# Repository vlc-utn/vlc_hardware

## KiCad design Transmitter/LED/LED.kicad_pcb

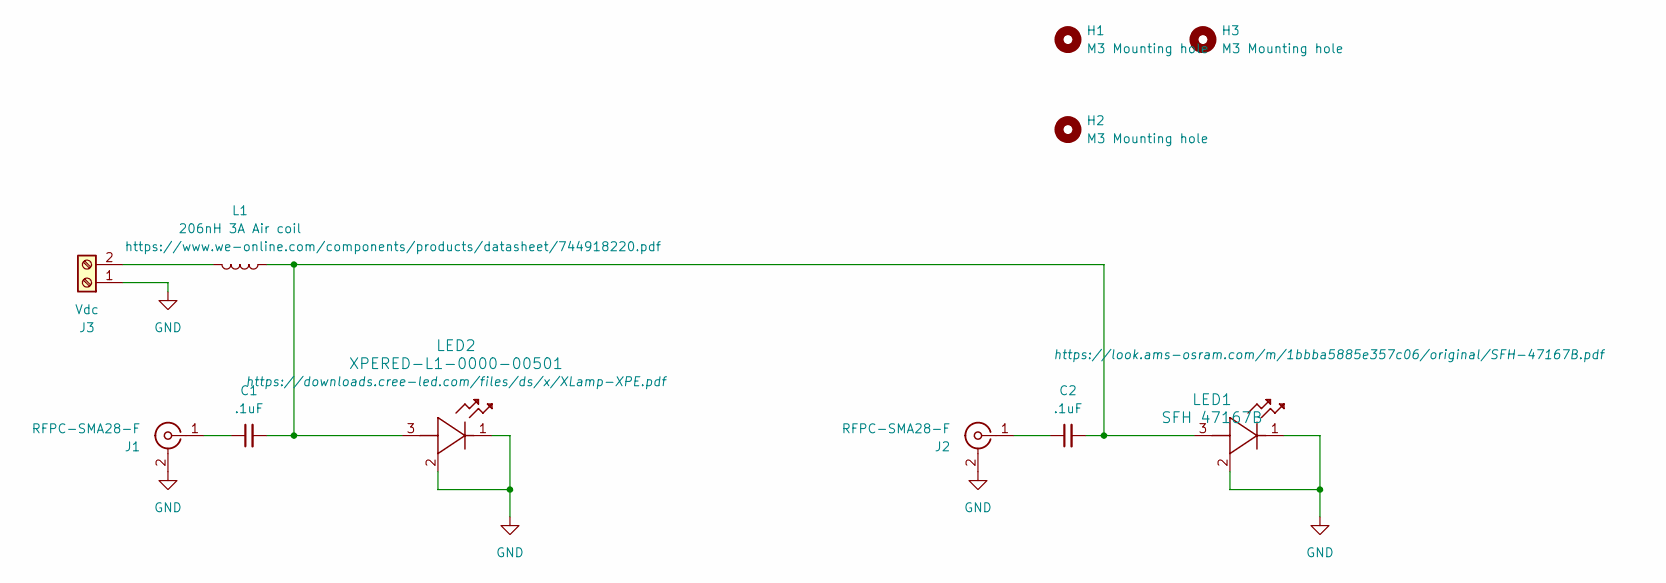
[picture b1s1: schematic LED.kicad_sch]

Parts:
C1, C2: .1uF; C_0402_1005Metric_Pad0.74x0.62mm_HandSolder; Manufacturer Part Number 530L104KT16; Mouser Part Number 581-530L104KT16
H1, H2, H3: M3 Mounting hole; MountingHole_3.2mm_M3_DIN965
J1, J2: RFPC-SMA28-F; Manufacturer Part Number RFPC-SMA28-F; Mouser Part Number 640-RFPCSMA28F
J3: Vdc; TerminalBlock_Phoenix_MKDS-1,5-2_1x02_P5.00mm_Horizontal
L1: 206nH 3A Air coil; L_Wurth_WE-CAIR-5910; Manufacturer Part Number 744918220; Mouser Part Number 710-744918220
LED1: SFH 47167B
LED2: XPERED-L1-0000-00501; LED_CREE_XPLx

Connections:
GND: J1.2 (Ext), J2.2 (Ext), J3.1, LED1.1 (cathode), LED1.2 (thermal), LED2.1 (cathode), LED2.2 (thermal)
unnamed: C1.1, J1.1 (In)
unnamed: C2.1, J2.1 (In)
unnamed: J3.2, L1.2
unnamed: C1.2, C2.2, L1.1, LED1.3 (anode), LED2.3 (anode)

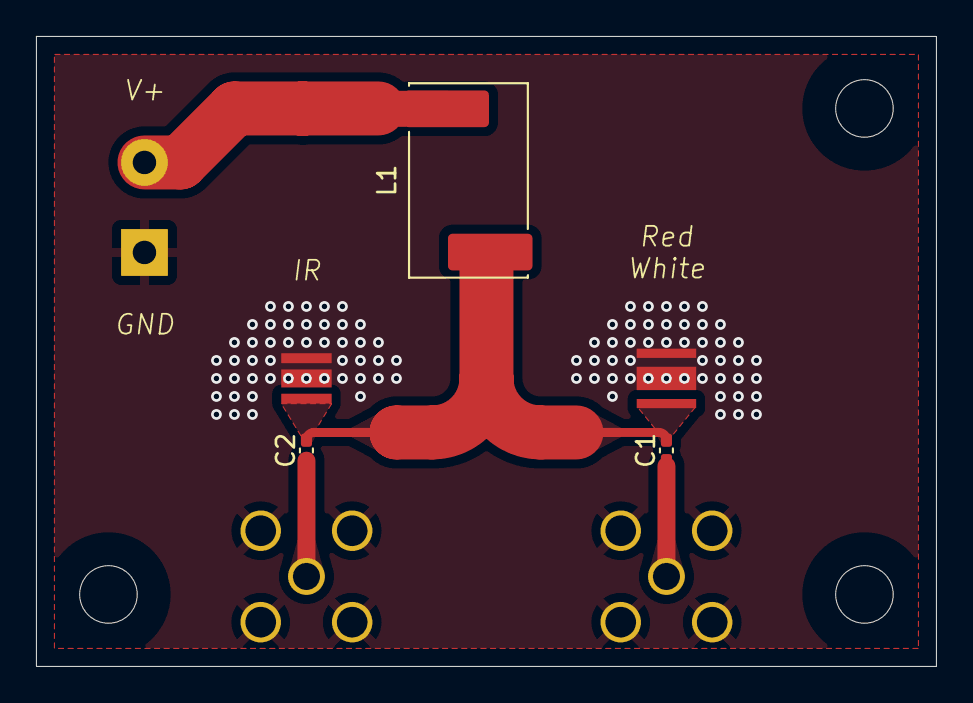
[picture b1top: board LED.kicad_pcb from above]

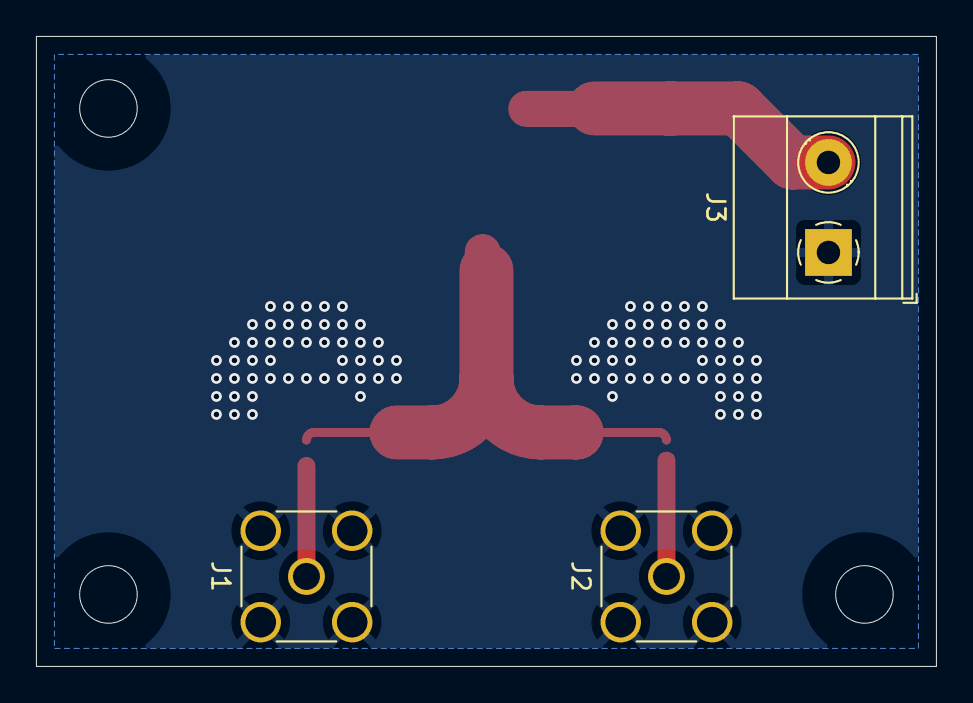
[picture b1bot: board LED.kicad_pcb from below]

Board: 2 copper layers, 50.0 x 35.0 mm, 11 parts (3 on the bottom side), 5 nets.

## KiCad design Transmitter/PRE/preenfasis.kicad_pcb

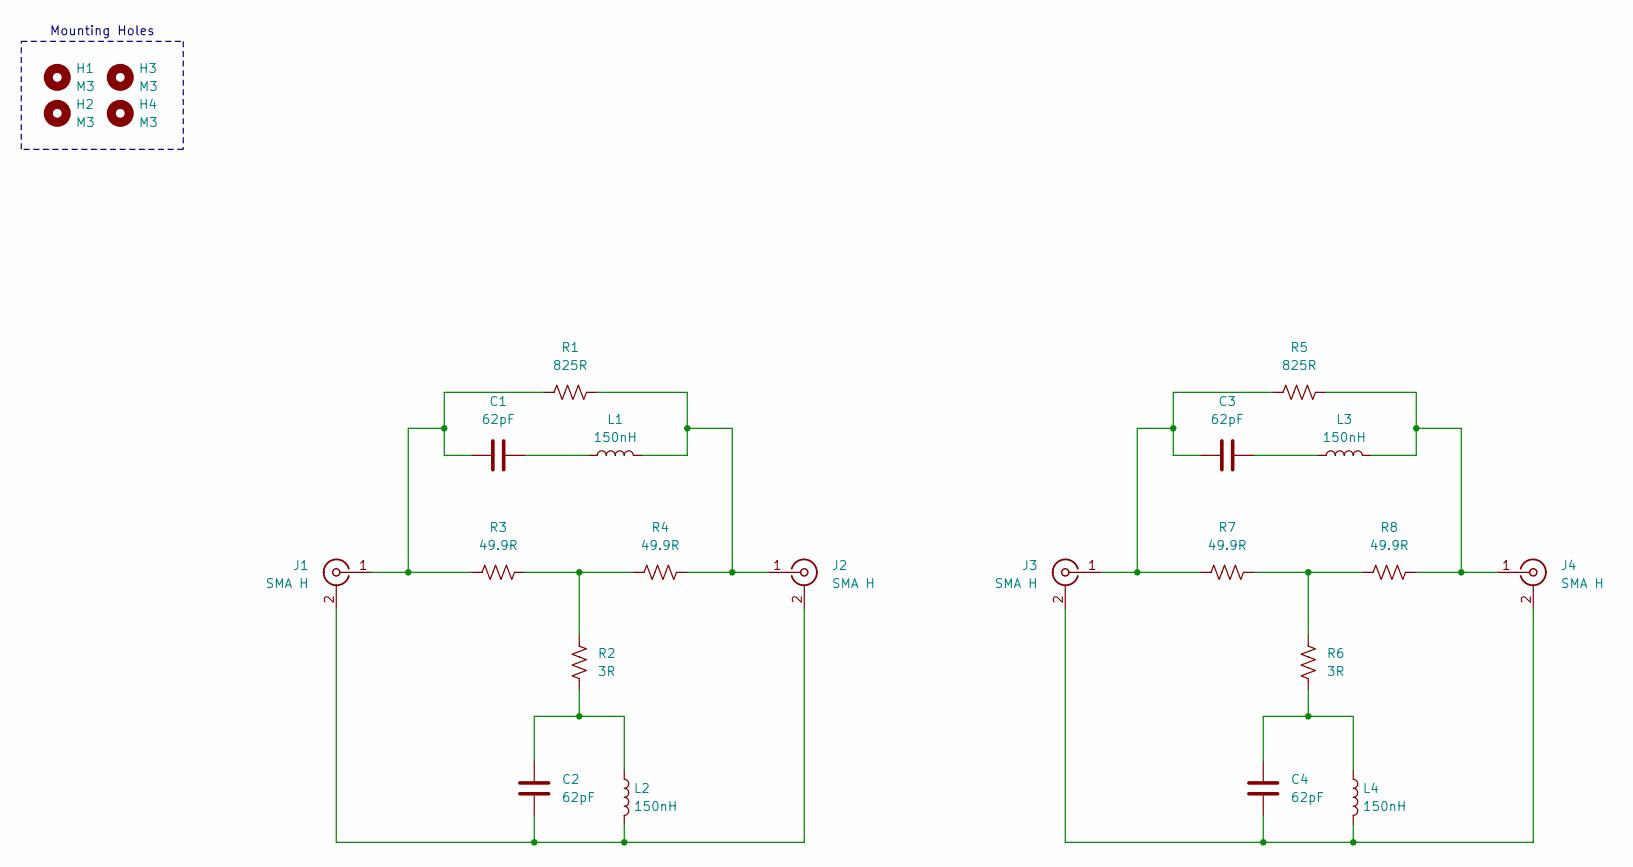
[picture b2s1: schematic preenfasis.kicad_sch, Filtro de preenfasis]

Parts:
C1, C2, C3, C4: 62pF; C_0603_1608Metric_Pad1.08x0.95mm_HandSolder; Manufacturer P/N CC0603JRNPO9BN620; Mouser P/N 603-CC603JRNPO9BN620
H1, H2, H3, H4: M3; MountingHole_3.2mm_M3_ISO7380; Manufacturer P/N N/A; Mouser P/N N/A
J1, J2, J3, J4: SMA H; SMA_Samtec_SMA-J-P-X-ST-EM1_EdgeMount; Manufacturer P/N Electrocomponentes; Mouser P/N N/A
L1, L2, L3, L4: 150nH; L_0603_1608Metric_Pad1.05x0.95mm_HandSolder; Manufacturer P/N MLJ1608WR15JT000; Mouser P/N 810-MLJ1608WR15JT000
R1, R5: 825R; R_0603_1608Metric_Pad0.98x0.95mm_HandSolder; Manufacturer P/N RT0603FRE07825RL; Mouser P/N 603-RT0603FRE07825RL
R2, R6: 3R; R_0603_1608Metric_Pad0.98x0.95mm_HandSolder; Manufacturer P/N RT0603FRE073RL; Mouser P/N 603-RT0603FRE073RL
R3, R4, R7, R8: 49.9R; R_0603_1608Metric_Pad0.98x0.95mm_HandSolder; Manufacturer P/N RT0603FRE0749R9L; Mouser P/N 603-RT0603FRE0749R9L

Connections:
unnamed: C1.2, L1.1
unnamed: C2.2, L2.1, R2.2
unnamed: C3.2, L3.1
unnamed: C4.2, L4.1, R6.2
unnamed: C2.1, J1.2 (Ext), J2.2 (Ext), L2.2
unnamed: C1.1, J1.1 (In), R1.1, R3.1
unnamed: J2.1 (In), L1.2, R1.2, R4.2
unnamed: C4.1, J3.2 (Ext), J4.2 (Ext), L4.2
unnamed: C3.1, J3.1 (In), R5.1, R7.1
unnamed: J4.1 (In), L3.2, R5.2, R8.2
unnamed: R2.1, R3.2, R4.1
unnamed: R6.1, R7.2, R8.1

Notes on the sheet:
Mounting Holes

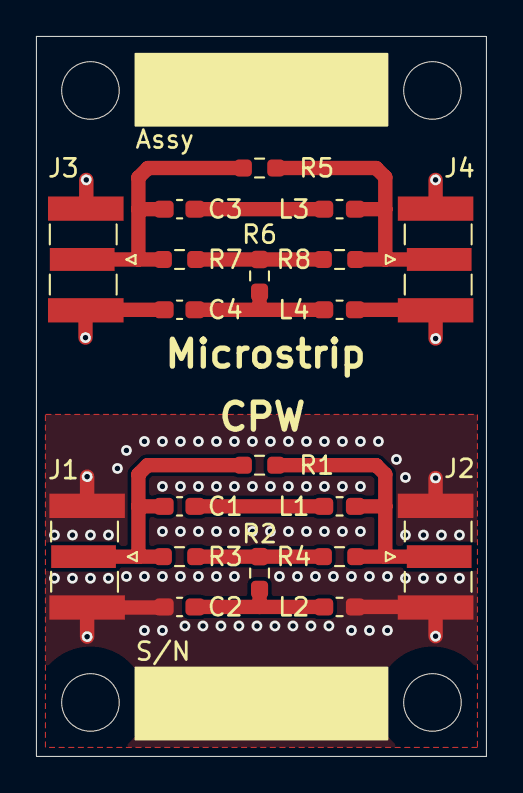
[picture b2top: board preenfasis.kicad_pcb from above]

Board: 2 copper layers, 25.0 x 40.0 mm, 24 parts (0 on the bottom side), 12 nets.

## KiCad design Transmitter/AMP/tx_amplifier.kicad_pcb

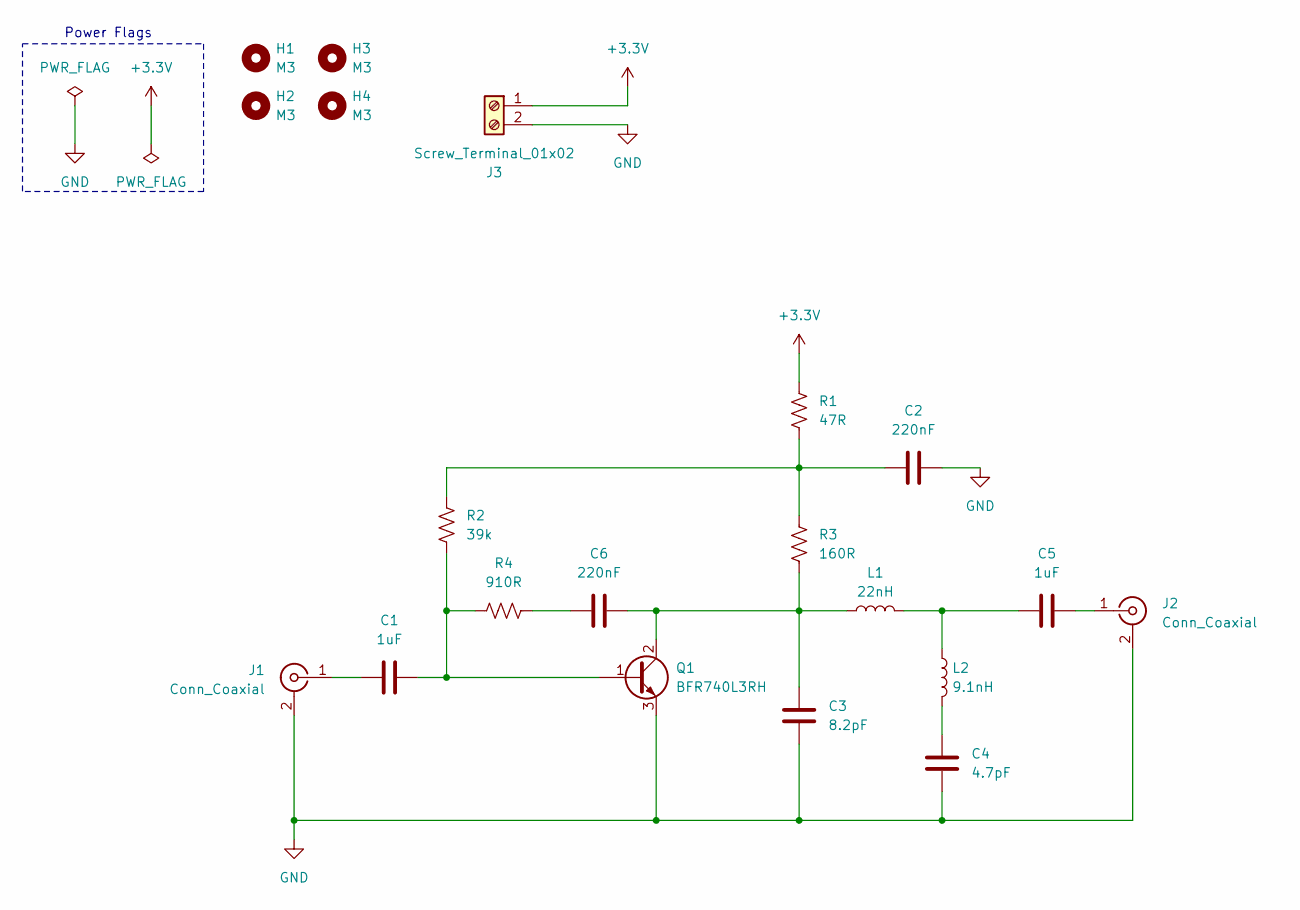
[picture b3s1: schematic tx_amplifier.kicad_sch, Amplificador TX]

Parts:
C1, C5: 1uF; C_0603_1608Metric_Pad1.08x0.95mm_HandSolder; Manufacturer P/N SH18B105K160CT; Mouser P/N 791-SH18B105K160CT
C2, C6: 220nF; C_0603_1608Metric_Pad1.08x0.95mm_HandSolder; Manufacturer P/N 0603B224K250CT; Mouser P/N 791-0603B224K250CT
C3: 8.2pF; C_0603_1608Metric_Pad1.08x0.95mm_HandSolder; Manufacturer P/N 0603N8R2C500CT; Mouser P/N 791-0603N8R2C500CT
C4: 4.7pF; C_0603_1608Metric_Pad1.08x0.95mm_HandSolder; Manufacturer P/N 0603N4R7C500CT; Mouser P/N 791-0603N4R7C500CT
H1, H2, H3, H4: M3; MountingHole_3.2mm_M3_ISO7380; Manufacturer P/N N/A; Mouser P/N N/A
J1, J2: Conn_Coaxial; SMA_Samtec_SMA-J-P-X-ST-EM1_EdgeMount; Manufacturer P/N SMA-KE1.2mm; Mouser P/N N/A
J3: Screw_Terminal_01x02; TerminalBlock_bornier-2_P5.08mm; Manufacturer P/N VI0221550000G; Mouser P/N 649-220316-H021B01LF
L1: 22nH; L_0603_1608Metric_Pad1.05x0.95mm_HandSolder; Manufacturer P/N 7847806220; Mouser P/N 710-7847806220
L2: 9.1nH; L_0603_1608Metric_Pad1.05x0.95mm_HandSolder; Manufacturer P/N LQW18AN9N1C00D; Mouser P/N 81-LQW18AN9N1C00D
Q1: BFR740L3RH; TSLP-3-9; Manufacturer P/N BFR740L3RHE6327XTSA1; Mouser P/N 726-BFR740L3RHE6327X
R1: 47R; R_1206_3216Metric_Pad1.30x1.75mm_HandSolder; Manufacturer P/N RC1206FR-0747RL; Mouser P/N 603-RC1206FR-0747RL
R2: 39k; R_0603_1608Metric_Pad0.98x0.95mm_HandSolder; Manufacturer P/N RT0603FRE0739KL; Mouser P/N 603-RT0603FRE0739KL
R3: 160R; R_1206_3216Metric_Pad1.30x1.75mm_HandSolder; Manufacturer P/N RC1206FR-07160RL; Mouser P/N 603-RC1206FR-07160RL
R4: 910R; R_0603_1608Metric_Pad0.98x0.95mm_HandSolder; Manufacturer P/N RT0603FRE07910RL; Mouser P/N 603-RT0603FRE07910RL

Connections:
+3.3V: J3.1, R1.2
GND: C2.2, C3.1, C4.1, J1.2 (Ext), J2.2 (Ext), J3.2, Q1.3 (E)
unnamed: C2.1, R1.1, R2.2, R3.2
unnamed: C4.2, L2.2
unnamed: C5.1, L1.2, L2.1
unnamed: C6.1, R4.1
unnamed: C1.1, J1.1 (In)
unnamed: C5.2, J2.1 (In)
unnamed: C1.2, Q1.1 (B), R2.1, R4.2
unnamed: C3.2, C6.2, L1.1, Q1.2 (C), R3.1

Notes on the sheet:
Power Flags

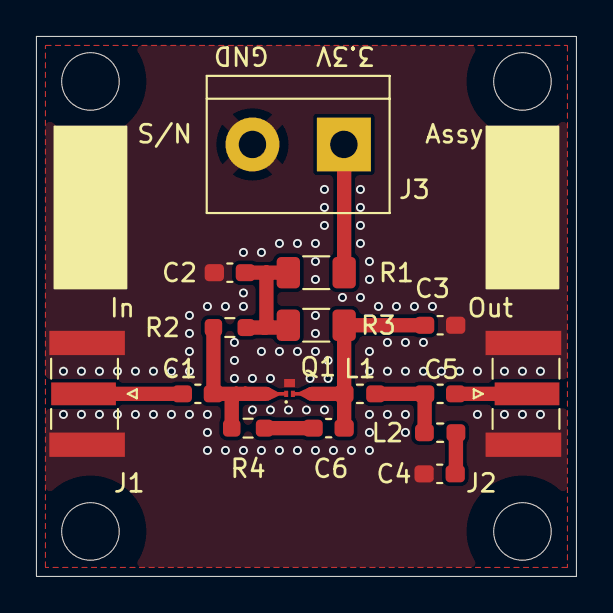
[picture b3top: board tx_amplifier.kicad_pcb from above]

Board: 2 copper layers, 30.0 x 30.0 mm, 20 parts (0 on the bottom side), 10 nets.

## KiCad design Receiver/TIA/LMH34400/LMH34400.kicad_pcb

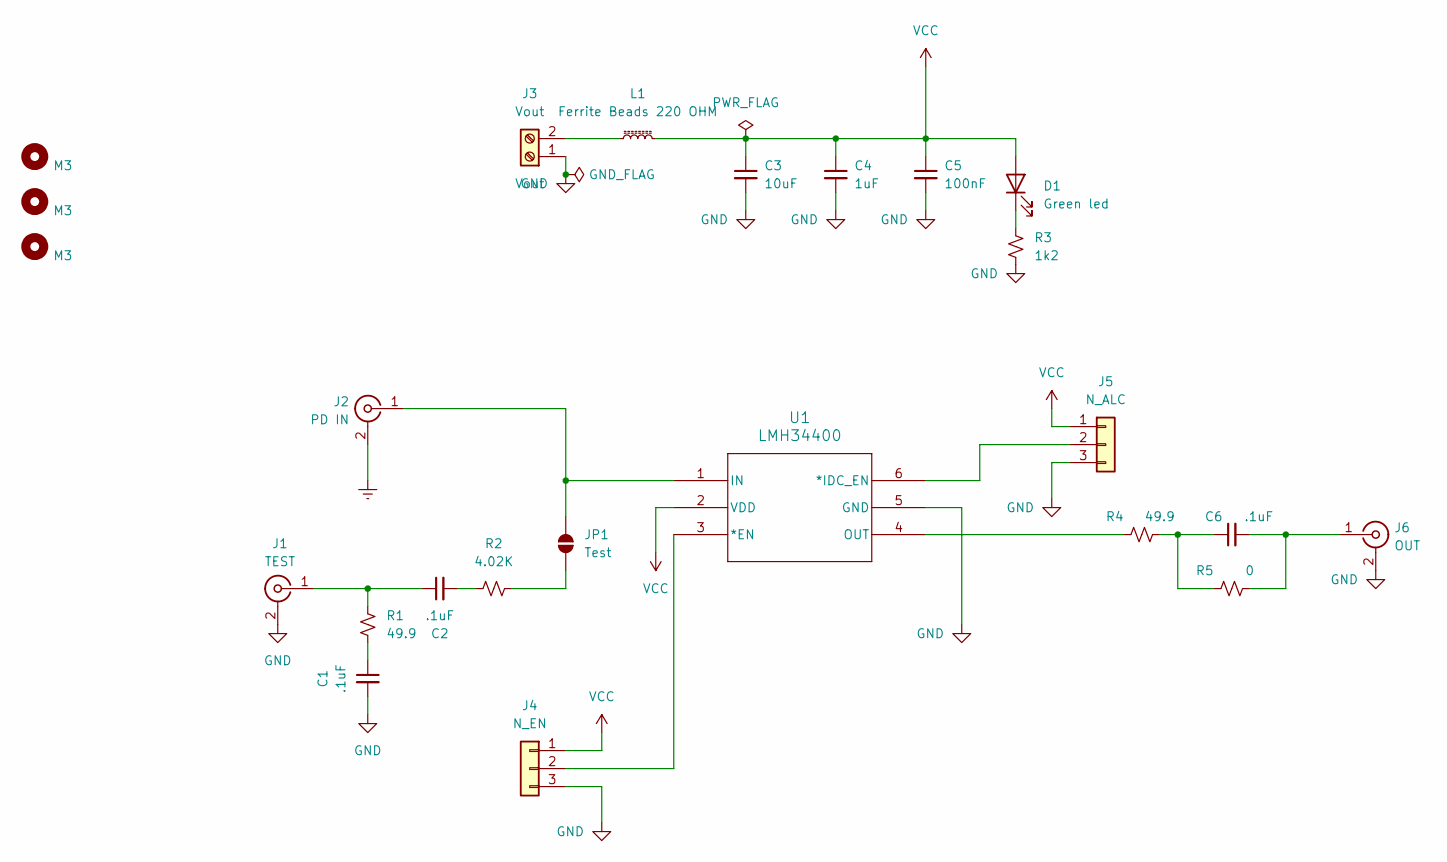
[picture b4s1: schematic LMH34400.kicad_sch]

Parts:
C1, C2, C6: .1uF; C_0402_1005Metric_Pad0.74x0.62mm_HandSolder; Manufacturer Part Number 530L104KT16; Mouser Part Number 581-530L104KT16
C3: 10uF; C_0603_1608Metric_Pad1.08x0.95mm_HandSolder; Manufacturer Part Number GRM188Z71A106MA73D; Mouser Part Number 81-GRM188Z71A106MA3D
C4: 1uF; C_0603_1608Metric_Pad1.08x0.95mm_HandSolder; Manufacturer Part Number CL10B105KP8NNNC; Mouser Part Number 187-CL10B105KP8NNNC
C5: 100nF; C_0603_1608Metric_Pad1.08x0.95mm_HandSolder; Manufacturer Part Number CL10B104KO8NFNC; Mouser Part Number 187-CL10B104KO8NFNC
D1: Green led; LED_0603_1608Metric; Manufacturer Part Number 150060VS75000; Mouser Part Number 710-150060VS75000
H1, H2, H3: M3; MountingHole_3.2mm_M3_DIN965
J1: TEST; SMA_Samtec_SMA-J-P-X-ST-EM1_EdgeMount
J2: PD IN; SMA_Samtec_SMA-J-P-X-ST-EM1_EdgeMount
J3: Vout; TerminalBlock_Phoenix_MKDS-1,5-2_1x02_P5.00mm_Horizontal
J4: N_EN; PinHeader_1x03_P2.54mm_Vertical
J5: N_ALC; PinHeader_1x03_P2.54mm_Vertical
J6: OUT; SMA_Samtec_SMA-J-P-X-ST-EM1_EdgeMount
JP1: Test; R_0603_1608Metric_Pad0.98x0.95mm_HandSolder; Manufacturer Part Number MCT0603MZ0000ZP500; Mouser Part Number 594-MCT0603MZ0000ZP5
L1: Ferrite Beads 220 OHM; L_0603_1608Metric_Pad1.05x0.95mm_HandSolder; Manufacturer Part Number BLM18KG221SN1D; Mouser Part Number 81-BLM18KG221SN1D
R1, R4: 49.9; R_0603_1608Metric_Pad0.98x0.95mm_HandSolder; Manufacturer Part Number MCT06030C4999FP500; Mouser Part Number 594-MCT06030C4999FP5
R2: 4.02K; R_0603_1608Metric_Pad0.98x0.95mm_HandSolder; Manufacturer Part Number MCT06030C4021FP500; Mouser Part Number 594-MCT06030C4021FP5
R3: 1k2; R_0603_1608Metric_Pad0.98x0.95mm_HandSolder; Manufacturer Part Number CRCW06031K20FKEA; Mouser Part Number 71-CRCW0603-1.2K-E3
R5: 0; R_0603_1608Metric_Pad0.98x0.95mm_HandSolder; Manufacturer Part Number MCT0603MZ0000ZP500; Mouser Part Number 594-MCT0603MZ0000ZP5
U1: LMH34400; SOT5X3-6_DRL_TEX; Manufacturer Part Number LMH34400IDRLR; Mouser Part Number 595-LMH34400IDRLR

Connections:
GND: C1.2, C3.2, C4.2, C5.2, J1.2 (Ext), J2.2 (Ext), J3.1, J4.3, J5.3, J6.2 (Ext), R3.2, U1.5 (GND)
unnamed: C1.1, R1.2
unnamed: C2.2, R2.1
unnamed: C6.1, R4.2, R5.1
unnamed: D1.1 (K), R3.1
unnamed: C2.1, J1.1 (In), R1.1
unnamed: J2.1 (In), JP1.2 (B), U1.1 (IN)
unnamed: J3.2, L1.1
unnamed: J4.2, U1.3 (*EN)
unnamed: J5.2, U1.6 (*IDC_EN)
unnamed: C6.2, J6.1 (In), R5.2
unnamed: JP1.1 (A), R2.2
unnamed: R4.1, U1.4 (OUT)
VCC: C3.1, C4.1, C5.1, D1.2 (A), J4.1, J5.1, L1.2, U1.2 (VDD)

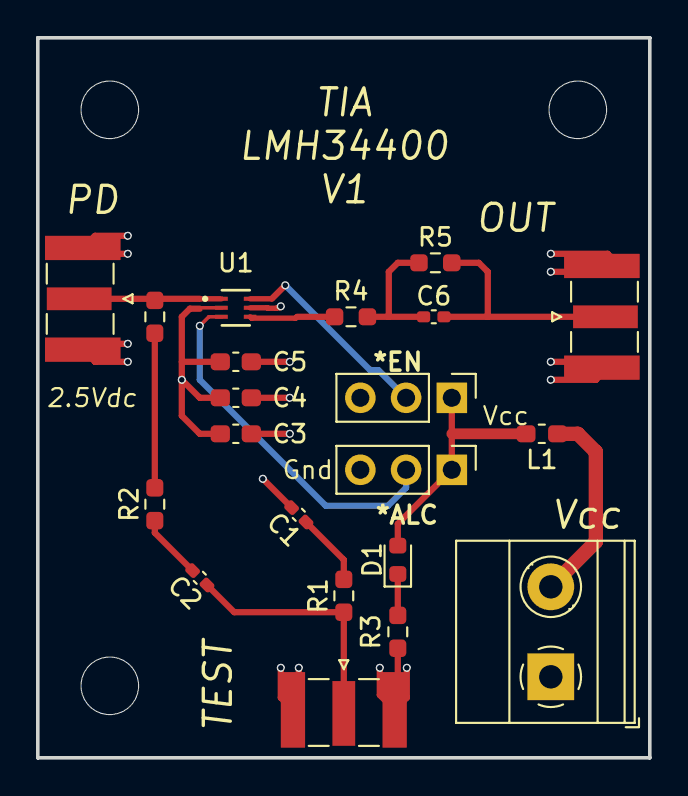
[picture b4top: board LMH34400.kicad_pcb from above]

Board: 4 copper layers, 34.0 x 40.0 mm, 24 parts (0 on the bottom side), 14 nets.

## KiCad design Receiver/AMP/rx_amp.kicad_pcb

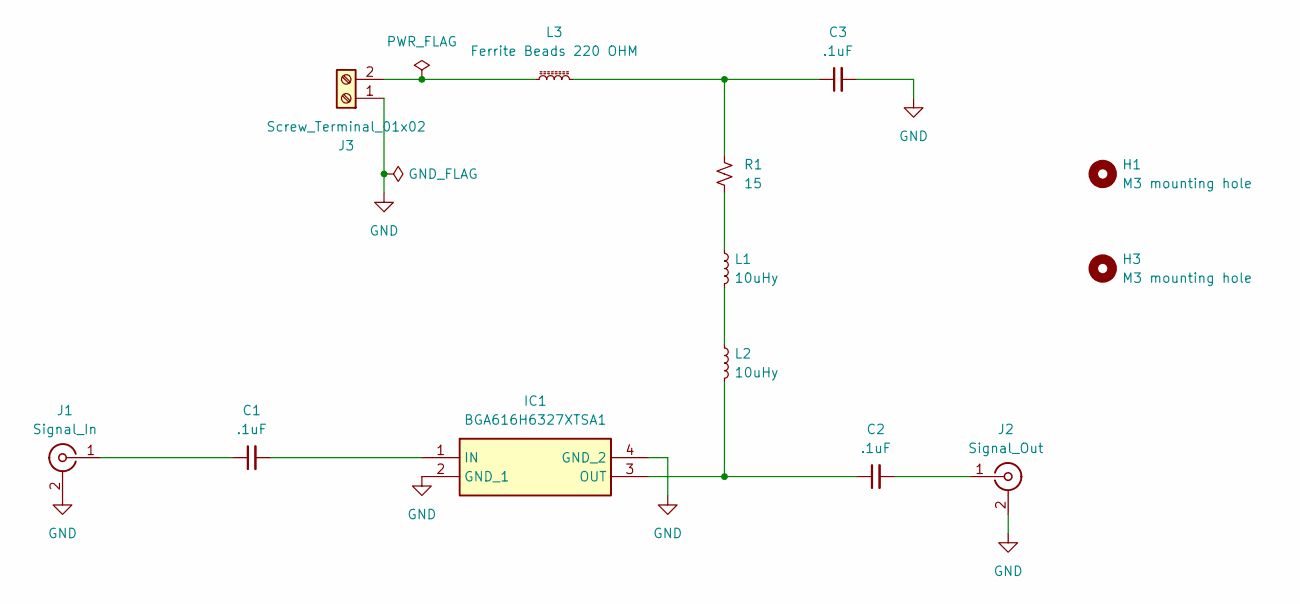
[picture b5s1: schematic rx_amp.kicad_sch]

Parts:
C1, C2, C3: .1uF; C_0402_1005Metric_Pad0.74x0.62mm_HandSolder; Mouser Part Number 581-530L104KT16
H1, H3: M3 mounting hole; MountingHole_3.2mm_M3_DIN965
IC1: BGA616H6327XTSA1; Mouser Part Number 726-BGA616H6327XTSA1
J1: Signal_In; SMA_Samtec_SMA-J-P-X-ST-EM1_EdgeMount
J2: Signal_Out; SMA_Samtec_SMA-J-P-X-ST-EM1_EdgeMount
J3: Screw_Terminal_01x02; TerminalBlock_RND_205-00001_1x02_P5.00mm_Horizontal
L1, L2: 10uHy; L_0603_1608Metric_Pad1.05x0.95mm_HandSolder; Mouser Part Number 81-LQM18DZ100M70L
L3: Ferrite Beads 220 OHM; L_0603_1608Metric_Pad1.05x0.95mm_HandSolder; Mouser Part Number 81-BLM18KG221SN1D
R1: 15; L_0603_1608Metric_Pad1.05x0.95mm_HandSolder; Mouser Part Number 710-560112116150

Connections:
GND: C3.2, IC1.2 (GND_1), IC1.4 (GND_2), J1.2 (Ext), J2.2 (Ext), J3.1
unnamed: C3.1, L3.2, R1.1
unnamed: C1.2, IC1.1 (IN)
unnamed: C2.1, IC1.3 (OUT), L2.2
unnamed: C1.1, J1.1 (In)
unnamed: C2.2, J2.1 (In)
unnamed: J3.2, L3.1
unnamed: L1.1, R1.2
unnamed: L1.2, L2.1

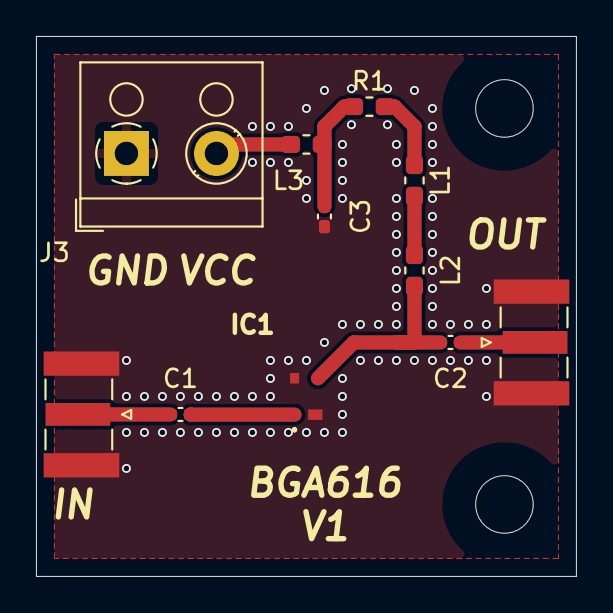
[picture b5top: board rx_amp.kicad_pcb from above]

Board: 2 copper layers, 30.0 x 30.0 mm, 13 parts (0 on the bottom side), 9 nets.

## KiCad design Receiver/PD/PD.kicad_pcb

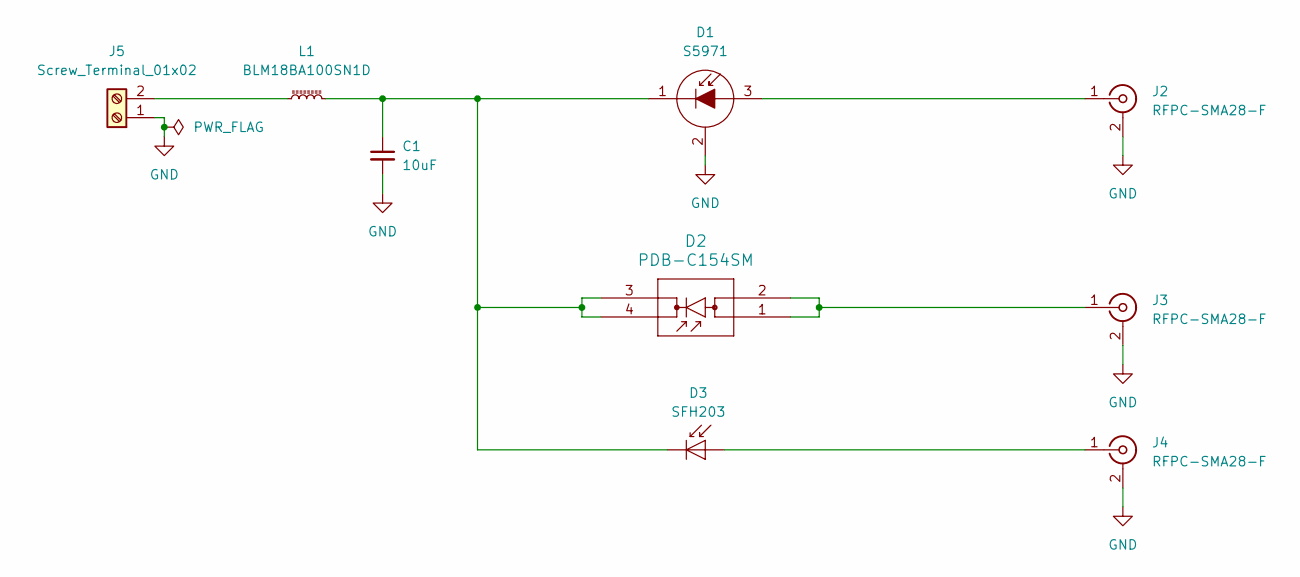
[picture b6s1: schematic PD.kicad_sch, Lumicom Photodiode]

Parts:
C1: 10uF; C_0603_1608Metric_Pad1.08x0.95mm_HandSolder
D1: S5971; TO-18-3; Mfr P/N S5971
D2: PDB-C154SM; PDB-C154SM_ADP; Mfr P/N PDB-C154SM; Mouser P/N 846-PDB-C154SM
D3: SFH203; LED_D5.0mm_IRGrey; Mfr P/N SFH 203 P; Mouser P/N 720-SFH203P
J2, J3, J4: RFPC-SMA28-F
J5: Screw_Terminal_01x02; TerminalBlock_bornier-2_P5.08mm
L1: BLM18BA100SN1D; L_0603_1608Metric_Pad1.05x0.95mm_HandSolder

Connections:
GND: C1.2, D1.2 (C), J2.2 (Ext), J3.2 (Ext), J4.2 (Ext), J5.1
unnamed: D1.3 (A), J2.1 (In)
unnamed: C1.1, D1.1 (K), D2.3 (CATHODE), D2.4 (CATHODE), D3.1 (K), L1.2
unnamed: D3.2 (A), J4.1 (In)
unnamed: D2.1 (ANODE), D2.2 (ANODE), J3.1 (In)
unnamed: J5.2, L1.1

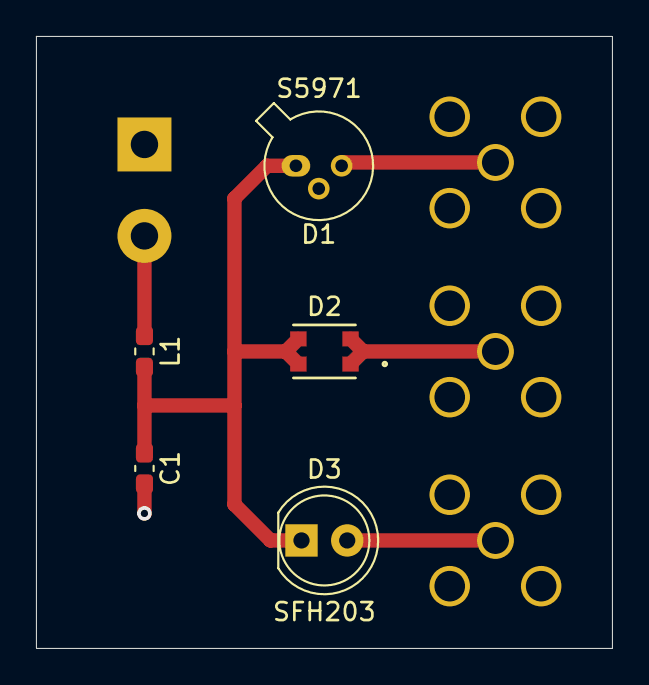
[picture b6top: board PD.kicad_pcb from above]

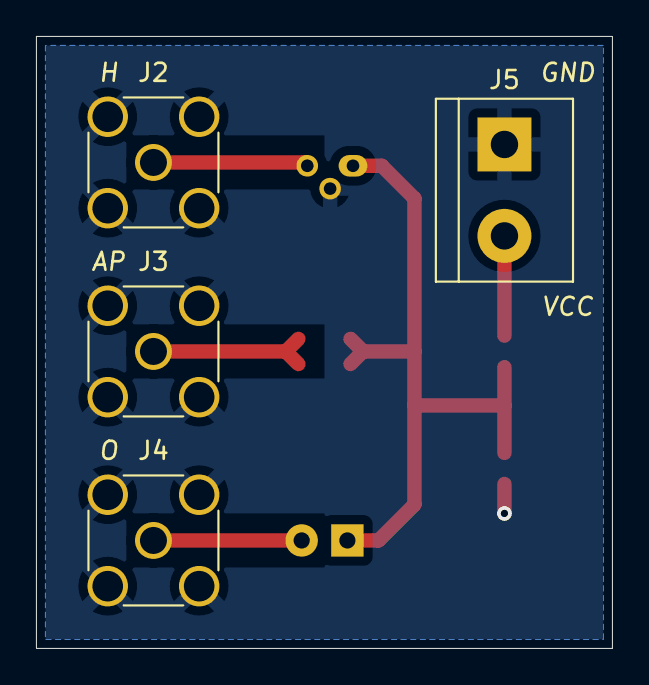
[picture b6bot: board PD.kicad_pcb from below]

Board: 2 copper layers, 32.0 x 34.0 mm, 9 parts (4 on the bottom side), 6 nets.

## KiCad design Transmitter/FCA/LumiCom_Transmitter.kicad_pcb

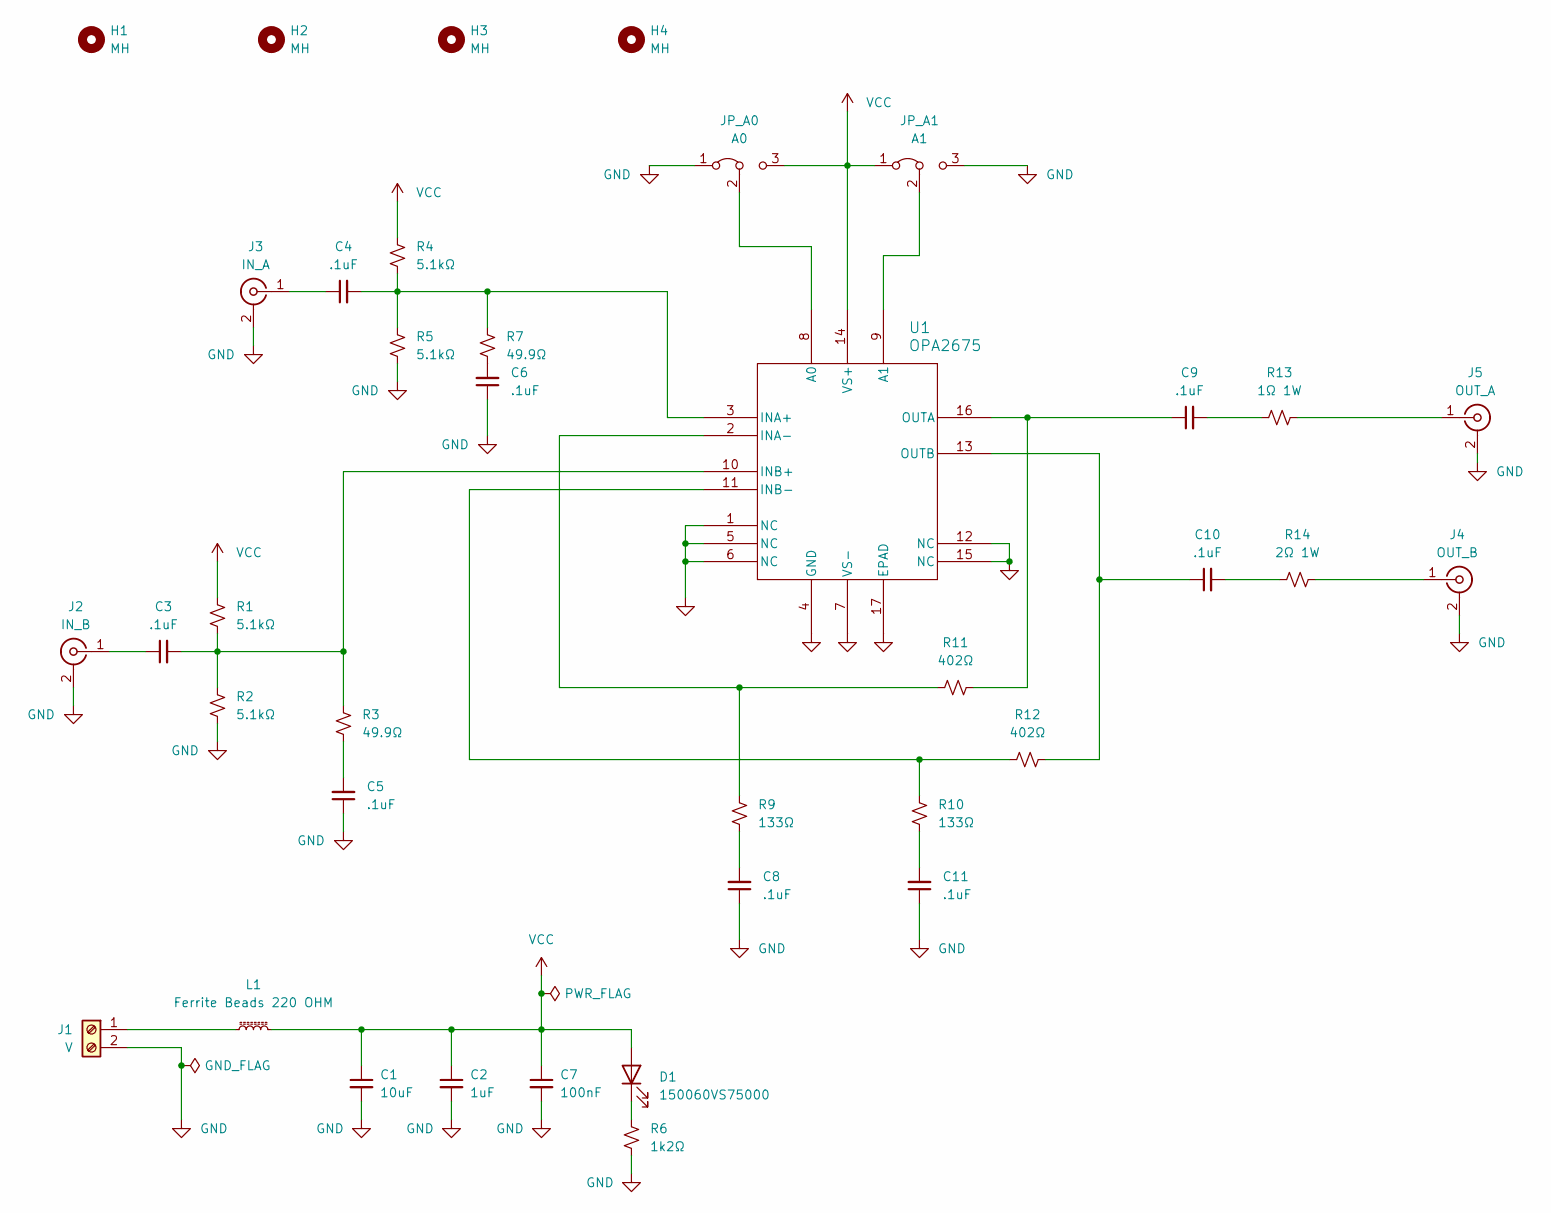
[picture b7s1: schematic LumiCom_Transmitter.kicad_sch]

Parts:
C1: 10uF; C_0603_1608Metric_Pad1.08x0.95mm_HandSolder; Manufacturer Part Number GRM188Z71A106MA73D; Mouser Part Number 81-GRM188Z71A106MA3D
C2: 1uF; C_0603_1608Metric_Pad1.08x0.95mm_HandSolder; Manufacturer Part Number CL10B105KP8NNNC; Mouser Part Number 187-CL10B105KP8NNNC
C3, C4, C5, C6, C8, C9, C10, C11: .1uF; C_0402_1005Metric_Pad0.74x0.62mm_HandSolder; Manufacturer Part Number 530L104KT16; Mouser Part Number 581-530L104KT16
C7: 100nF; C_0603_1608Metric_Pad1.08x0.95mm_HandSolder; Manufacturer Part Number CL10B104KO8NFNC; Mouser Part Number 187-CL10B104KO8NFNC
D1: 150060VS75000; LEDC1608X80N; Manufacturer Part Number 150060VS75000; Mouser Part Number 710-150060VS75000
H1, H2, H3, H4: MH; MountingHole_3.2mm_M3_ISO7380
J1: V; TerminalBlock_Phoenix_MKDS-1,5-2_1x02_P5.00mm_Horizontal
J2: IN_B; SMA_Samtec_SMA-J-P-X-ST-EM1_EdgeMount
J3: IN_A; SMA_Samtec_SMA-J-P-X-ST-EM1_EdgeMount
J4: OUT_B; SMA_Samtec_SMA-J-P-X-ST-EM1_EdgeMount
J5: OUT_A; SMA_Samtec_SMA-J-P-X-ST-EM1_EdgeMount
JP_A0: A0; PinHeader_1x03_P2.54mm_Vertical
JP_A1: A1; PinHeader_1x03_P2.54mm_Vertical
L1: Ferrite Beads 220 OHM; L_0603_1608Metric_Pad1.05x0.95mm_HandSolder; Manufacturer Part Number BLM18KG221SN1D; Mouser Part Number 81-BLM18KG221SN1D
R1, R2, R4, R5: 5.1kΩ; R_0603_1608Metric; Manufacturer Part Number CRCW06035K10FKEA; Mouser Part Number 71-CRCW0603-5.1K-E3
R3, R7: 49.9Ω; R_0603_1608Metric; Manufacturer Part Number MCT06030C4999FP500; Mouser Part Number 594-MCT06030C4999FP5
R6: 1k2Ω; R_0603_1608Metric_Pad0.98x0.95mm_HandSolder; Manufacturer Part Number CRCW06031K20FKEA; Mouser Part Number 71-CRCW0603-1.2K-E3
R9, R10: 133Ω; R_0402_1005Metric_Pad0.72x0.64mm_HandSolder; Manufacturer Part Number CRT0402-FZ-1330GLF; Mouser Part Number 652-CRT0402FZ1330GLF
R11, R12: 402Ω; R_0402_1005Metric_Pad0.72x0.64mm_HandSolder; Manufacturer Part Number CRT0402-FZ-4020GLF; Mouser Part Number 652-CRT0402FZ4020GLF
R13: 1Ω 1W; R_1206_3216Metric_Pad1.30x1.75mm_HandSolder; Manufacturer Part Number RNCL1206FT1R00; Mouser Part Number 708-RNCL1206FT1R00
R14: 2Ω 1W; R_1206_3216Metric_Pad1.30x1.75mm_HandSolder; Manufacturer Part Number RNCL1206FT2R00; Mouser Part Number 708-RNCL1206FT2R00
U1: OPA2675; Texas_OPA2675; Manufacturer Part Number OPA2675RGVR; Mouser Part Number 595-OPA2675RGVR

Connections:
GND: C1.2, C2.2, C5.1, C6.1, C7.2, C8.1, C11.1, J1.2, J2.2 (Ext), J3.2 (Ext), J4.2 (Ext), J5.2 (Ext), JP_A0.1 (A), JP_A1.3 (B), R2.2, R5.2, R6.2, U1.1 (NC), U1.4 (GND), U1.5 (NC), U1.6 (NC), U1.7 (VS-), U1.12 (NC), U1.15 (NC), U1.17 (EPAD)
unnamed: C5.2, R3.2
unnamed: C6.2, R7.2
unnamed: C8.2, R9.1
unnamed: C9.2, R13.1
unnamed: C10.2, R14.1
unnamed: C11.2, R10.1
unnamed: D1.1 (K), R6.1
unnamed: J1.1, L1.1
unnamed: C3.1, J2.1 (In)
unnamed: C4.1, J3.1 (In)
unnamed: J4.1 (In), R14.2
unnamed: J5.1 (In), R13.2
unnamed: JP_A0.2 (C), U1.8 (A0)
unnamed: JP_A1.2 (C), U1.9 (A1)
unnamed: C4.2, R4.2, R5.1, R7.1, U1.3 (INA+)
unnamed: R9.2, R11.1, U1.2 (INA-)
unnamed: C3.2, R1.2, R2.1, R3.1, U1.10 (INB+)
unnamed: R10.2, R12.1, U1.11 (INB-)
unnamed: C9.1, R11.2, U1.16 (OUTA)
unnamed: C10.1, R12.2, U1.13 (OUTB)
VCC: C1.1, C2.1, C7.1, D1.2 (A), JP_A0.3 (B), JP_A1.1 (A), L1.2, R1.1, R4.1, U1.14 (VS+)

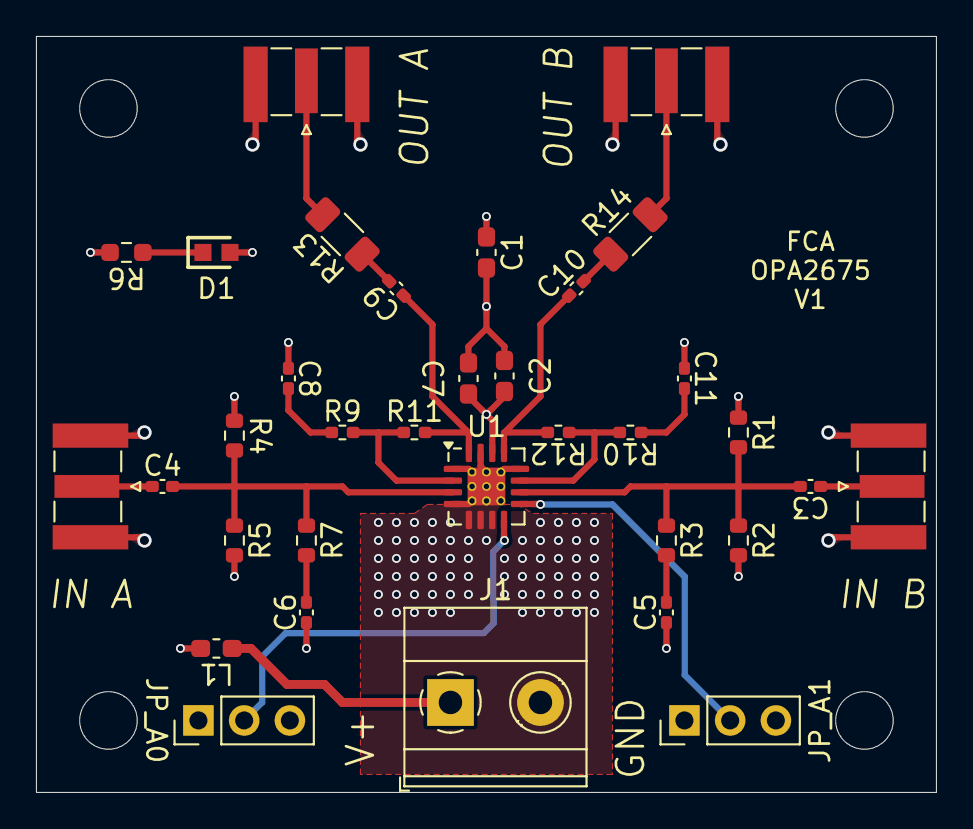
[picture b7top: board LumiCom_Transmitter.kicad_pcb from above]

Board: 4 copper layers, 50.0 x 42.0 mm, 38 parts (0 on the bottom side), 22 nets.
